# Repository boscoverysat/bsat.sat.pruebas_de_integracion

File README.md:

# Prebas de Integración

## Resumen

Este repositrio contiene tanto el código como la circuitería necesaria para poder realizar la implementación del satélite.

## Elementos

### [Processing](processing/)

Contiene el código empleado para poder llevar a cabo la representación gráfica del comportamiento del satélite.

### [PCB](pcb/)

Contiene los diseños y esquemas eléctricos correspondientes a las placas de circuito impreso empleadas para el satélite.

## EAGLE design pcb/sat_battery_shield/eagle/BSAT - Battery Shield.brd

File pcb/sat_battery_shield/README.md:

# SAT Battery Shield

## Resumen

Esta sección del repositorio contiene el circuito electrónico y el diseño de placa de circuito impreso para el sistema de alimentación del satélite.

El diseño electrónico se ha llevado a cabo mediante el software **Eagle PCB**.

#### Diseño PCB

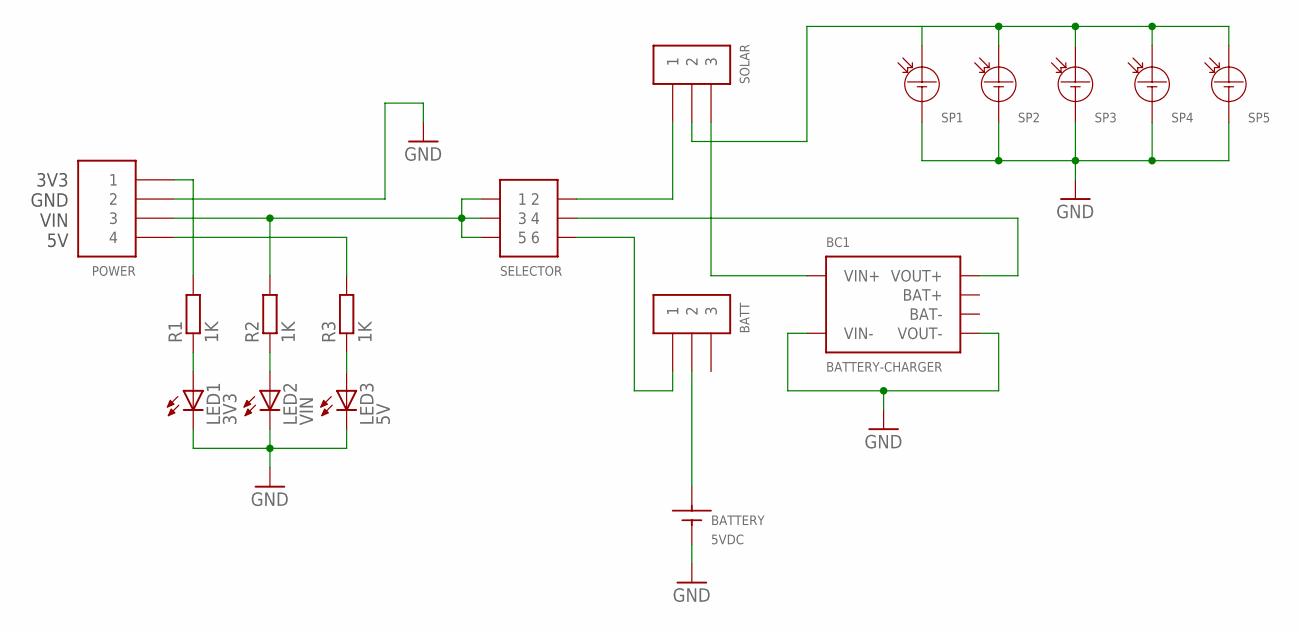
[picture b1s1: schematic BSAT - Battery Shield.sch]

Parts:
5VDC: BATTERY; SOLAR-PANEL
BATT: 3-PIN-JUMPER
BC1: BATTERY-CHARGER
LED1: 3V3; LED3MM
LED2: VIN; LED3MM
LED3: 5V; LED3MM
POWER: 4-PIN-DUAL-BUS; 4-PIN-LINEAL-JUMPER
R1, R2, R3: 1K; 0207/12
SELECTOR: 3-PIN-PARALEL-JUMPER
SOLAR: 3-PIN-JUMPER
SP1, SP2, SP3, SP4, SP5: SOLAR-PANEL2; SOLAR-PANEL

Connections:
GND: 5VDC.NEG, BC1.VIN-, BC1.VOUT-, LED1.K (C), LED2.K (C), LED3.K (C), POWER.2A (2), POWER.2B (2), SP1.NEG, SP2.NEG, SP3.NEG, SP4.NEG, SP5.NEG
unnamed: SELECTOR.2, SOLAR.1
unnamed: SOLAR.2, SP1.POS, SP2.POS, SP3.POS, SP4.POS, SP5.POS
unnamed: BC1.VIN+, SOLAR.3
unnamed: BC1.VOUT+, SELECTOR.4
unnamed: BATT.1, SELECTOR.6
unnamed: 5VDC.POS, BATT.2
unnamed: LED1.A, R1.1
unnamed: POWER.3A (3), POWER.3B (3), R2.2, SELECTOR.1, SELECTOR.3, SELECTOR.5
unnamed: LED2.A, R2.1
unnamed: LED3.A, R3.1
unnamed: POWER.1A (1), POWER.1B (1), R1.2
unnamed: POWER.4A (4), POWER.4B (4), R3.2

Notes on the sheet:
3V3 GND VIN 5V

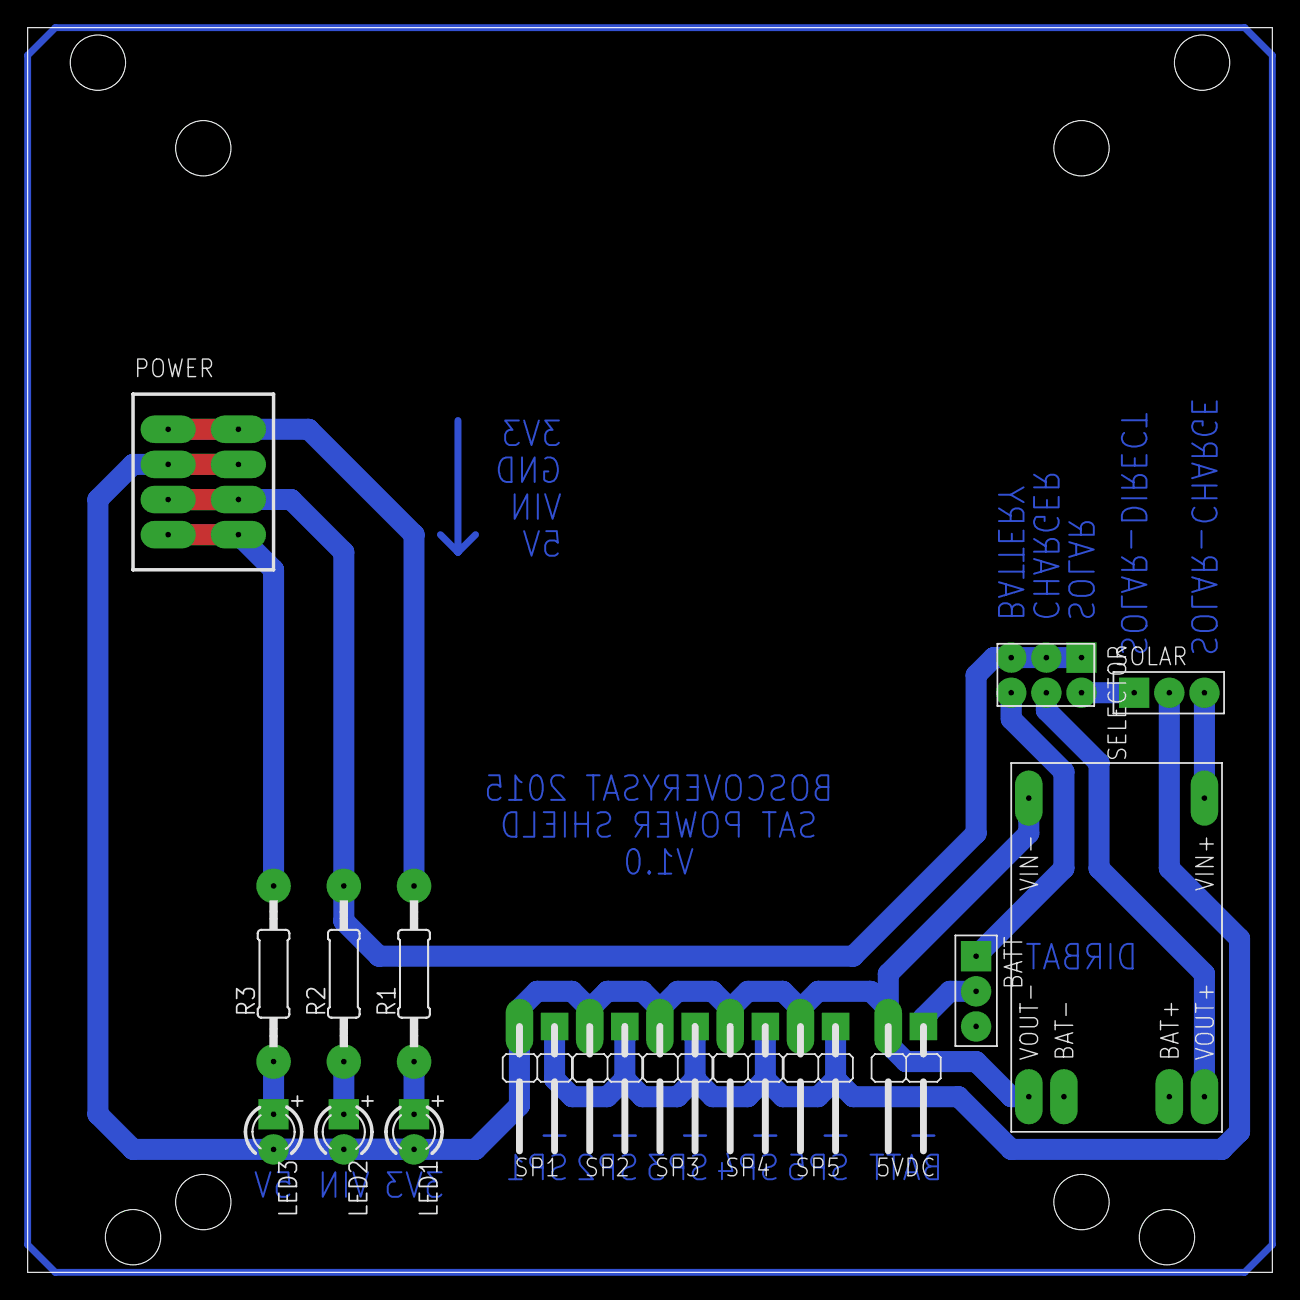
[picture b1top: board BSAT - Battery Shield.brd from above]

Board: 2 copper layers, 90.0 x 90.0 mm, 17 parts (0 on the bottom side), 13 nets.

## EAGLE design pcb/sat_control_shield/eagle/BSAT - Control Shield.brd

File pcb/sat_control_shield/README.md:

# SAT Control Shield

## Resumen

Esta sección del repositorio contiene el circuito electrónico y el diseño de placa de circuito impreso para el sistema de control del satélite.

El diseño electrónico se ha llevado a cabo mediante el software **Eagle PCB**.

#### Diseño PCB

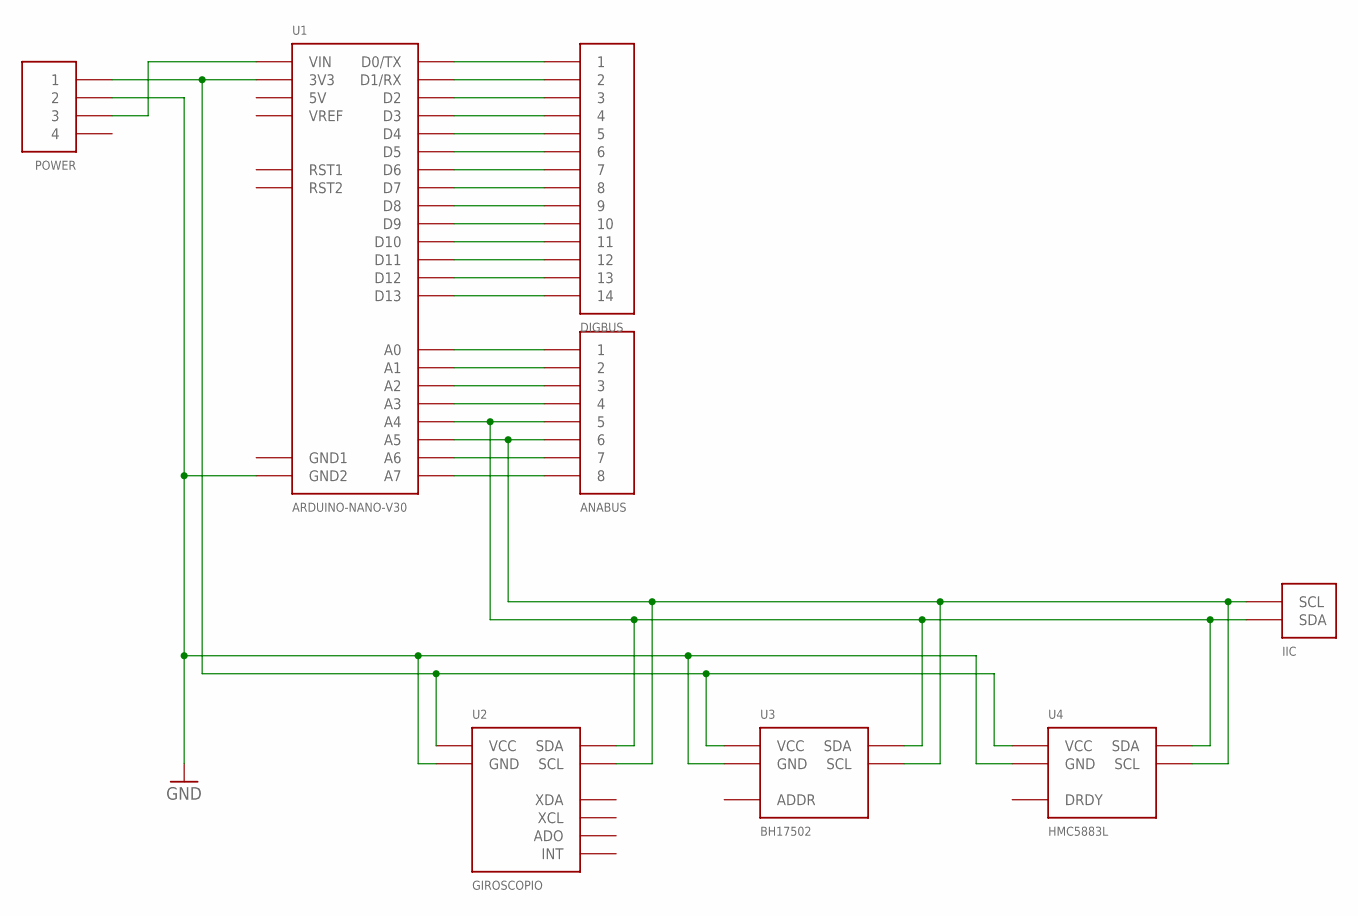
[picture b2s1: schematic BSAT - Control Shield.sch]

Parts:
ANABUS: 8-PIN-DUAL-BUS
DIGBUS: 14-PIN-DUAL-BUS
IIC: IIC-DUAL-BUS; 2-PIN-DUAL-BUS
POWER: 4-PIN-DUAL-BUS; 4-PIN-LINEAL-JUMPER
U1: ARDUINO-NANO-V30
U2: GIROSCOPIO
U3: BH17502; BH1750-2
U4: HMC5883L

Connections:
5V: U1.5V
GND: POWER.2A (2), POWER.2B (2), U1.GND2, U2.GND, U3.GND, U4.GND
GND1: U1.GND1
unnamed: DIGBUS.1A (1), DIGBUS.1B (1), U1.D0/TX
unnamed: DIGBUS.2A (2), DIGBUS.2B (2), U1.D1/RX
unnamed: POWER.3A (3), POWER.3B (3), U1.VIN
unnamed: POWER.1A (1), POWER.1B (1), U1.3V3, U2.VCC, U3.VCC, U4.VCC
unnamed: ANABUS.8A (8), ANABUS.8B (8), U1.A7
unnamed: ANABUS.7A (7), ANABUS.7B (7), U1.A6
unnamed: ANABUS.6A (6), ANABUS.6B (6), IIC.2A (SCL), IIC.2B (SCL), U1.A5, U2.SCL, U3.SCL, U4.SCL
unnamed: ANABUS.5A (5), ANABUS.5B (5), IIC.1A (SDA), IIC.1B (SDA), U1.A4, U2.SDA, U3.SDA, U4.SDA
unnamed: ANABUS.4A (4), ANABUS.4B (4), U1.A3
unnamed: ANABUS.3A (3), ANABUS.3B (3), U1.A2
unnamed: ANABUS.2A (2), ANABUS.2B (2), U1.A1
unnamed: ANABUS.1A (1), ANABUS.1B (1), U1.A0
unnamed: DIGBUS.3A (3), DIGBUS.3B (3), U1.D2
unnamed: DIGBUS.4A (4), DIGBUS.4B (4), U1.D3
unnamed: DIGBUS.5A (5), DIGBUS.5B (5), U1.D4
unnamed: DIGBUS.6A (6), DIGBUS.6B (6), U1.D5
unnamed: DIGBUS.7A (7), DIGBUS.7B (7), U1.D6
unnamed: DIGBUS.8A (8), DIGBUS.8B (8), U1.D7
unnamed: DIGBUS.9A (9), DIGBUS.9B (9), U1.D8
unnamed: DIGBUS.10A (10), DIGBUS.10B (10), U1.D9
unnamed: DIGBUS.11A (11), DIGBUS.11B (11), U1.D10
unnamed: DIGBUS.12A (12), DIGBUS.12B (12), U1.D11
unnamed: DIGBUS.13A (13), DIGBUS.13B (13), U1.D12
unnamed: DIGBUS.14A (14), DIGBUS.14B (14), U1.D13
VREF: U1.VREF

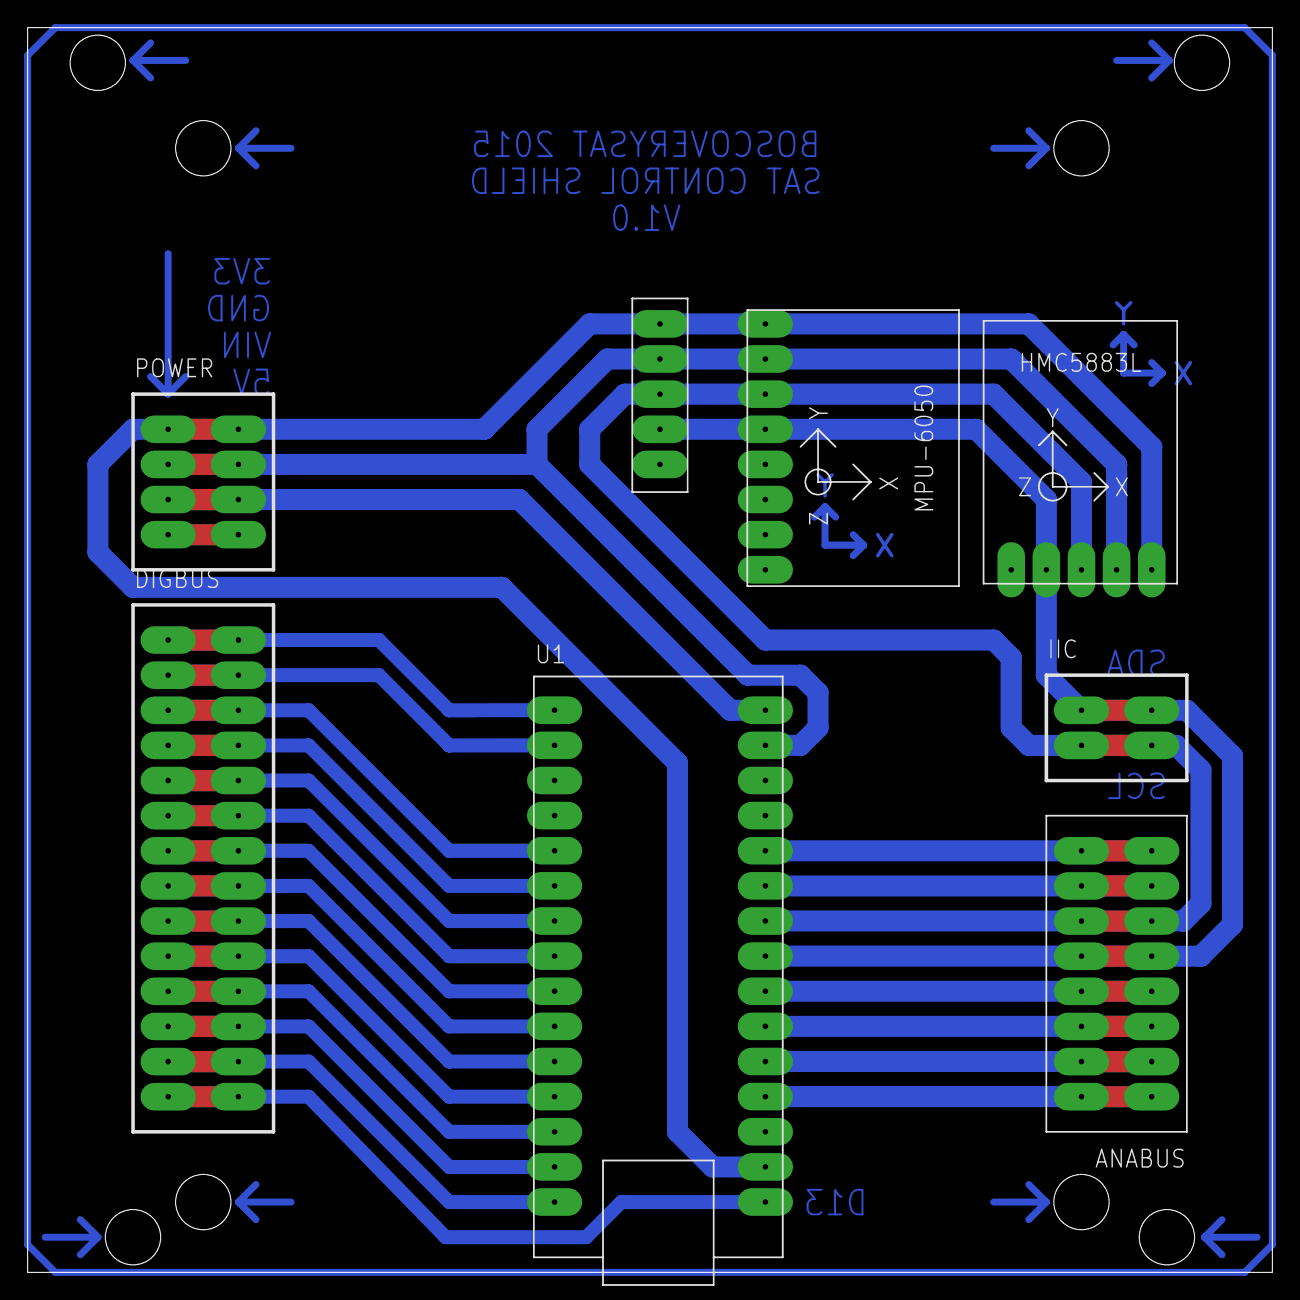
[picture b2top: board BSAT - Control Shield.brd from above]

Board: 2 copper layers, 90.0 x 90.0 mm, 8 parts (0 on the bottom side), 25 nets.

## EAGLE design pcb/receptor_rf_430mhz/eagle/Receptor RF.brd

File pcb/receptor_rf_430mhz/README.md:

# Receptor RF 430MHz

## Resumen

Esta sección del repositorio contiene el circuito electrónico y el diseño de placa de circuito impreso del receptor de radiofracuencia, para capturar localmente y mediante Arduino, los datos enviados desde el satélite.

El diseño electrónico se ha llevado a cabo mediante el software **Eagle PCB**.

#### Diseño PCB

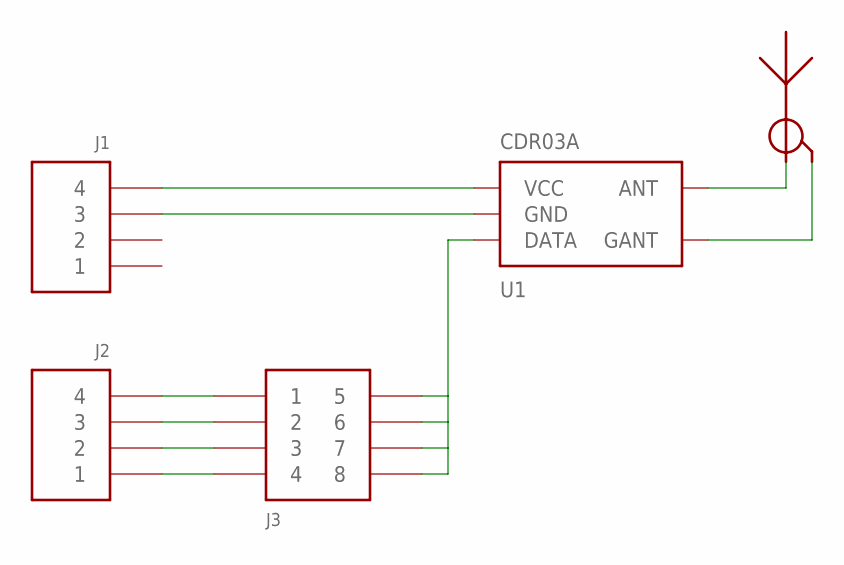
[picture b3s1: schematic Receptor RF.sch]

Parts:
J1, J2: 4-PIN-LINEAR-JUMPER
J3: 8-PIN-JUMPER
U1: CDR03A
U$3: ANTENNA

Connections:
unnamed: J1.P$4 (4), U1.VCC
unnamed: J1.P$3 (3), U1.GND
unnamed: J2.P$4 (4), J3.P$1 (1)
unnamed: U1.ANT, U$3.ANT
unnamed: U1.GANT, U$3.GANT
unnamed: J2.P$3 (3), J3.P$2 (2)
unnamed: J2.P$2 (2), J3.P$3 (3)
unnamed: J2.P$1 (1), J3.P$4 (4)
unnamed: J3.P$5 (5), J3.P$6 (6), J3.P$7 (7), J3.P$8 (8), U1.DATA1 (DATA), U1.DATA2 (DATA)

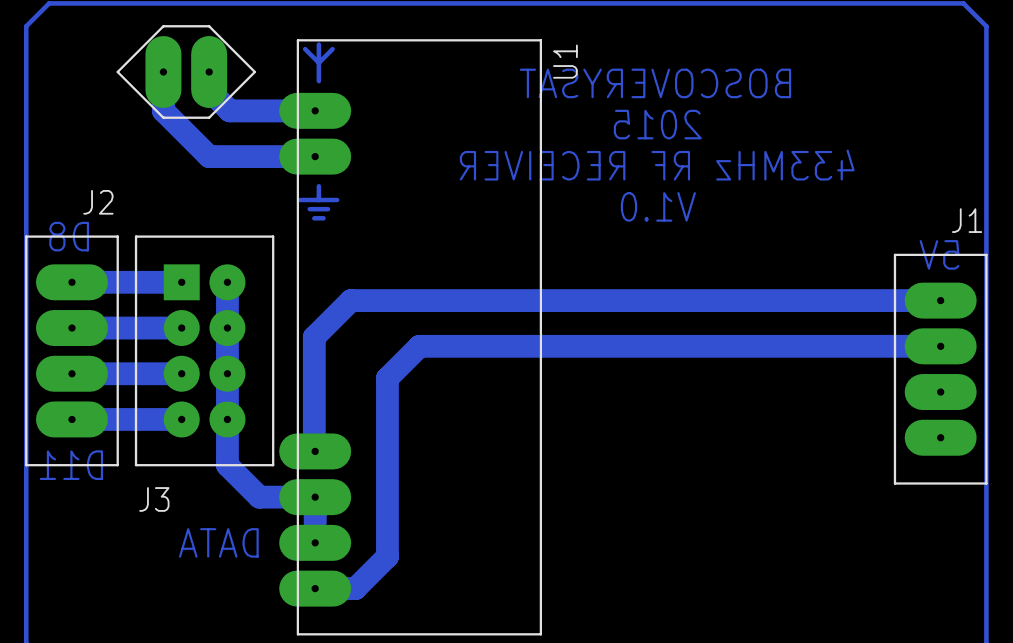
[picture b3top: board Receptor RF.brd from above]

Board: 2 copper layers, 5 parts (0 on the bottom side), 9 nets.

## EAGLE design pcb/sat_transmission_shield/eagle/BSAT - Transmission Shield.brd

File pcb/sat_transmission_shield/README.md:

# SAT Trasmission Shield

## Resumen

Esta sección del repositorio contiene el circuito electrónico y el diseño de placa de circuito impreso para el sistema de transmisión por radiofrecuencia del satélite.

El diseño electrónico se ha llevado a cabo mediante el software **Eagle PCB**.

#### Diseño PCB

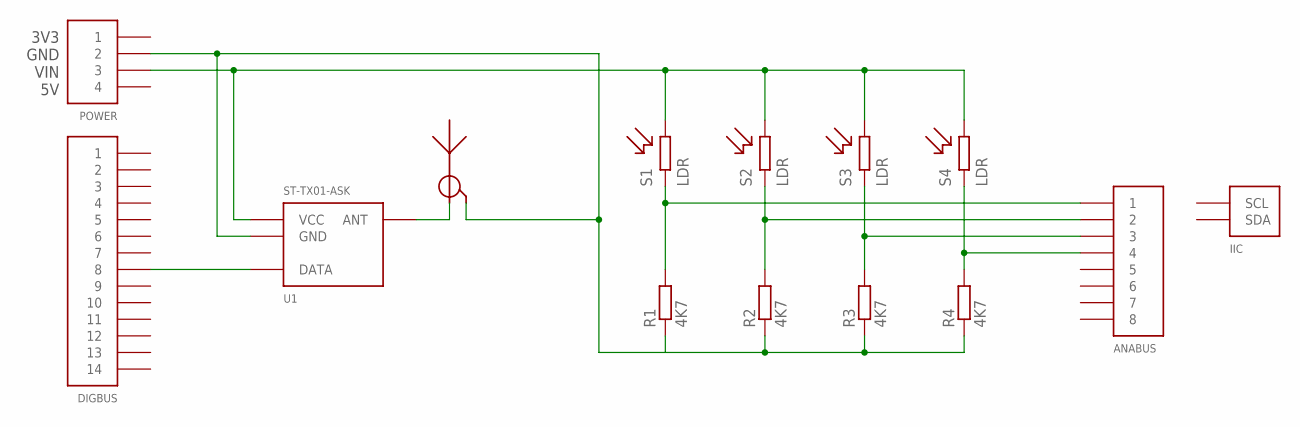
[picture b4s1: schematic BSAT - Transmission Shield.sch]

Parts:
ANABUS: 8-PIN-DUAL-BUS
DIGBUS: 14-PIN-DUAL-BUS
IIC: IIC-DUAL-BUS; 2-PIN-DUAL-BUS
POWER: 4-PIN-DUAL-BUS; 4-PIN-LINEAL-JUMPER
R1, R2, R3, R4: 4K7; 0207/12
S1, S2, S3, S4: LDR; 2-PIN-JUMPER
U1: ST-TX01-ASK
U$5: ANTENNA

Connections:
unnamed: ANABUS.1A (1), ANABUS.1B (1), R1.2, S1.P$2 (2)
unnamed: ANABUS.2A (2), ANABUS.2B (2), R2.2, S2.P$2 (2)
unnamed: ANABUS.3A (3), ANABUS.3B (3), R3.2, S3.P$2 (2)
unnamed: ANABUS.4A (4), ANABUS.4B (4), R4.2, S4.P$2 (2)
unnamed: POWER.3A (3), POWER.3B (3), S1.P$1 (1), S2.P$1 (1), S3.P$1 (1), S4.P$1 (1), U1.VCC
unnamed: DIGBUS.8A (8), DIGBUS.8B (8), U1.DATA
unnamed: POWER.2A (2), POWER.2B (2), R1.1, R2.1, R3.1, R4.1, U1.GND, U$5.GANT
unnamed: U1.ANT, U$5.ANT

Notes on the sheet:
3V3 GND VIN 5V

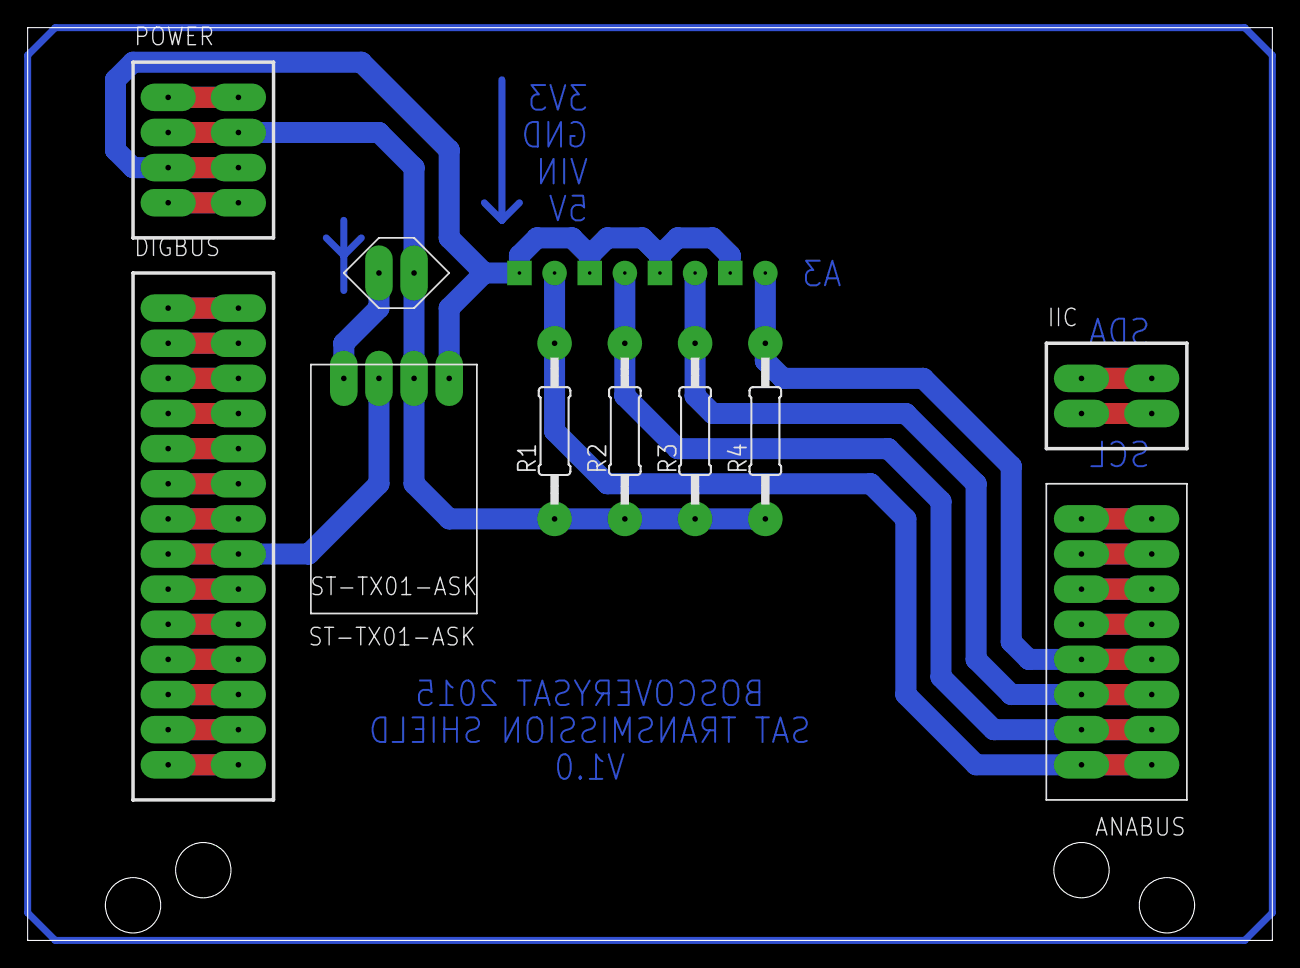
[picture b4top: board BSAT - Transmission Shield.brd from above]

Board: 2 copper layers, 90.0 x 66.0 mm, 14 parts (0 on the bottom side), 8 nets.

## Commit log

2015-11-07 Prototipo en desarrollo del software de Telemetría
2015-11-13 Con datos de prueba
2015-11-16 [ FEATURE ] - Añadidos esquemas y PCBs de satélite y receptor de RF.
2015-11-16 [ UPDATE ] - Actualizada imagen del PCB para el receptor de RF.
2015-11-16 Actualizado el Software
2015-11-17 Añadidos logos y zona para la representación 3D
2015-11-18 Software Estación de Tierra
2015-11-18 Añadida la carpeta Arduino
2015-11-20 [ UPDATE ] - Añadiendo procesamiento de telemetría mediante NodeJS.
2015-11-20 [ REPO CONFIG ] - Añadido archivo .gitignore.
2015-11-20 [ REPO UPDATE ] - Carpeta de módulos de NodeJS eliminada.
2015-11-20 [ UPDATE ] - Archivo package.json editado.
2016-05-25 feat(battery-shield): Diseños basados en KiCAD añadidos.
2016-05-26 chore(gitignore): File updated in order to avoid track .DS_Store files.
2016-05-26 chore(boscoverysat-lib): Arduino Nano V3.0 and 443 transmisor schema symbols attached.
2016-05-26 feat(control-shield): KiCAD project created for this shield.
2016-05-27 chore(desktop-app): Working on.
2016-05-27 feat(boscoverysat-lib): Library edited.
2016-05-27 feat(control-shield): Working on.
2016-05-29 feat(boscoverysat-lib): Arduino Nano v3, sensor luminos BH1750 y emisor de radio CDT-88 añadidos a la librería.
2016-05-29 refactor(battery-shield): Esquema actualizado.
2016-05-29 refactor(control-shield): Esquema y PCB rediseñadas a la versión v1.1 mediante KiCAD.
2016-05-30 feat(boscoverysat-lib): Sensor de temperatura HTU21D añadido.
2016-05-30 feat(control-shield): Sensor de temperatura HTU21D añadido.
2016-06-03 chore(local): Actualización repositorio local
